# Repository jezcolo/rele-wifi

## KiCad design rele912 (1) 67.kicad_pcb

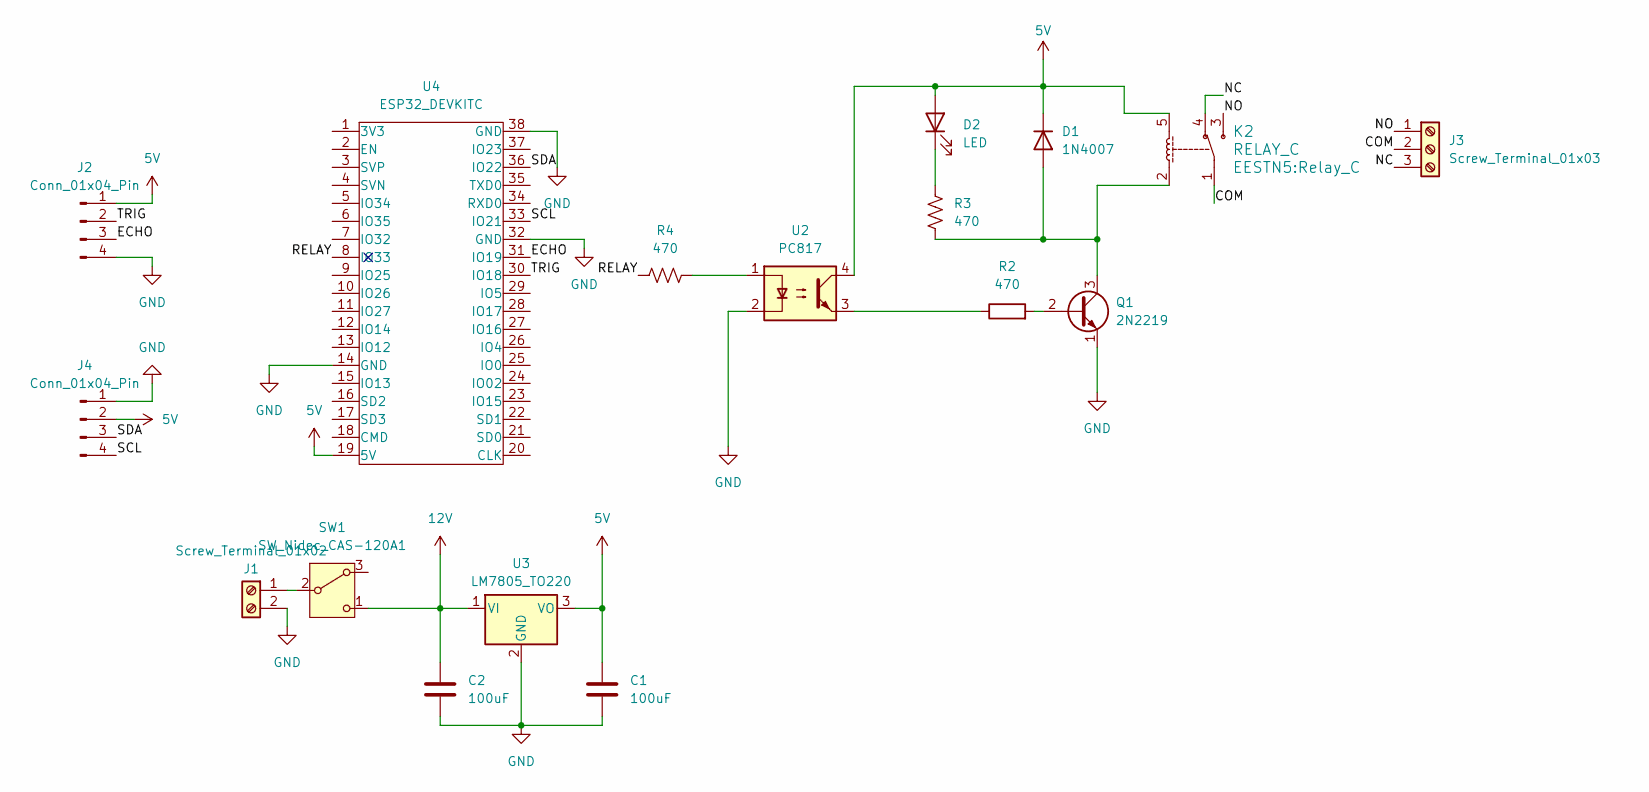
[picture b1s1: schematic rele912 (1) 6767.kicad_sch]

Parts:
C1, C2: 100uF; C_Disc_D3.0mm_W1.6mm_P2.50mm
D1: 1N4007; D_DO-41_SOD81_P10.16mm_Horizontal
D2: LED; LED_D1.8mm_W3.3mm_H2.4mm
J1: Screw_Terminal_01x02; TerminalBlock_MaiXu_MX126-5.0-02P_1x02_P5.00mm
J2, J4: Conn_01x04_Pin; PinHeader_1x04_P2.54mm_Vertical
J3: Screw_Terminal_01x03; TerminalBlock_MaiXu_MX126-5.0-03P_1x03_P5.00mm
K2: RELAY_C; Relay_C
Q1: 2N2219; TO-92
R2, R3, R4: 470; R_Axial_DIN0204_L3.6mm_D1.6mm_P7.62mm_Horizontal
SW1: SW_Nidec_CAS-120A1; PinHeader_1x02_P2.54mm_Vertical
U2: PC817; DIP-4_PC817
U3: LM7805_TO220; TO-220-3_Vertical
U4: ESP32_DEVKITC; MODULE_ESP32-DEVKITC

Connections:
5V: C1.1, D1.1 (K), D2.2 (A), J2.1, J4.2, K2.5, U2.4, U3.3 (VO), U4.19 (5V)
12V: C2.1, SW1.1 (C), U3.1 (VI)
/COM: J3.2, K2.1
/ECHO: J2.3, U4.31 (IO19)
/NC: J3.3, K2.4
/NO: J3.1, K2.3
/RELAY: R4.1, U4.8 (IO33)
/SCL: J4.4, U4.33 (IO21)
/SDA: J4.3, U4.36 (IO22)
/TRIG: J2.2, U4.30 (IO18)
GND: C1.2, C2.2, J1.2, J2.4, J4.1, Q1.1 (E), U2.2, U3.2 (GND), U4.14 (GND), U4.32 (GND), U4.38 (GND)
unnamed: D1.2 (A), K2.2, Q1.3 (C), R3.1
unnamed: D2.1 (K), R3.2
unnamed: J1.1, SW1.2 (B)
unnamed: Q1.2 (B), R2.2
unnamed: R2.1, U2.3
unnamed: R4.2, U2.1

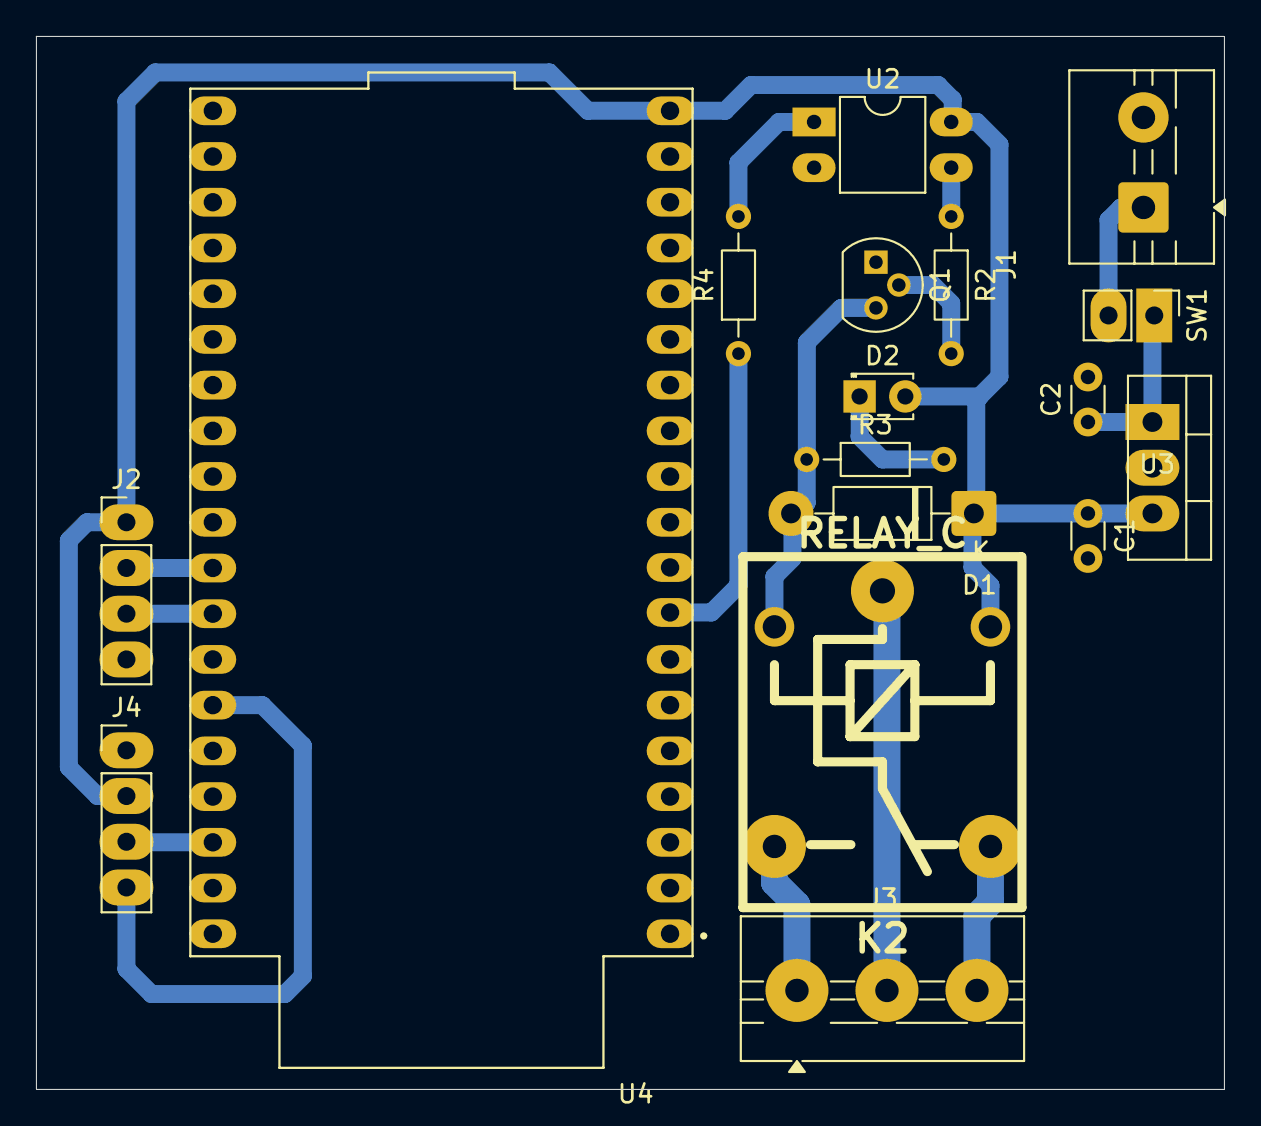
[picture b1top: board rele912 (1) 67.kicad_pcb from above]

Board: 2 copper layers, 66.0 x 58.5 mm, 17 parts (0 on the bottom side), 17 nets.
